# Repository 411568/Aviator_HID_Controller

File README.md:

<h2>🧐 Features</h2>

The goal of this project was to design a HID controller for interfacing a number of buttons and encoders with the X-Plane flight simulator software.

Here're some of the project's best features:

*  11 x button input
*  4 x rotary encoder input
*  1 x I2C interface connector
*  2 x 5V power output
*  USB type C for communication and power
*  HID keyboard interface

<h2>💻 Built with</h2>

Technologies used in the project:

*  STM32F072 microcontroller
*  ST1S06 buck converter
*  USB type C - HID communication
*  2-layer 0.8 mm FR4 PCB

<h2>🛡️ License:</h2>

This project is licensed under the MIT License.

<h2> 🙋‍♂️Authors </h2>

- Krzysztof Sikora

<h2>💖Like my work?</h2>

If you have any questions about the project feel free to contact us via email: krzysieksikora717@gmail.com

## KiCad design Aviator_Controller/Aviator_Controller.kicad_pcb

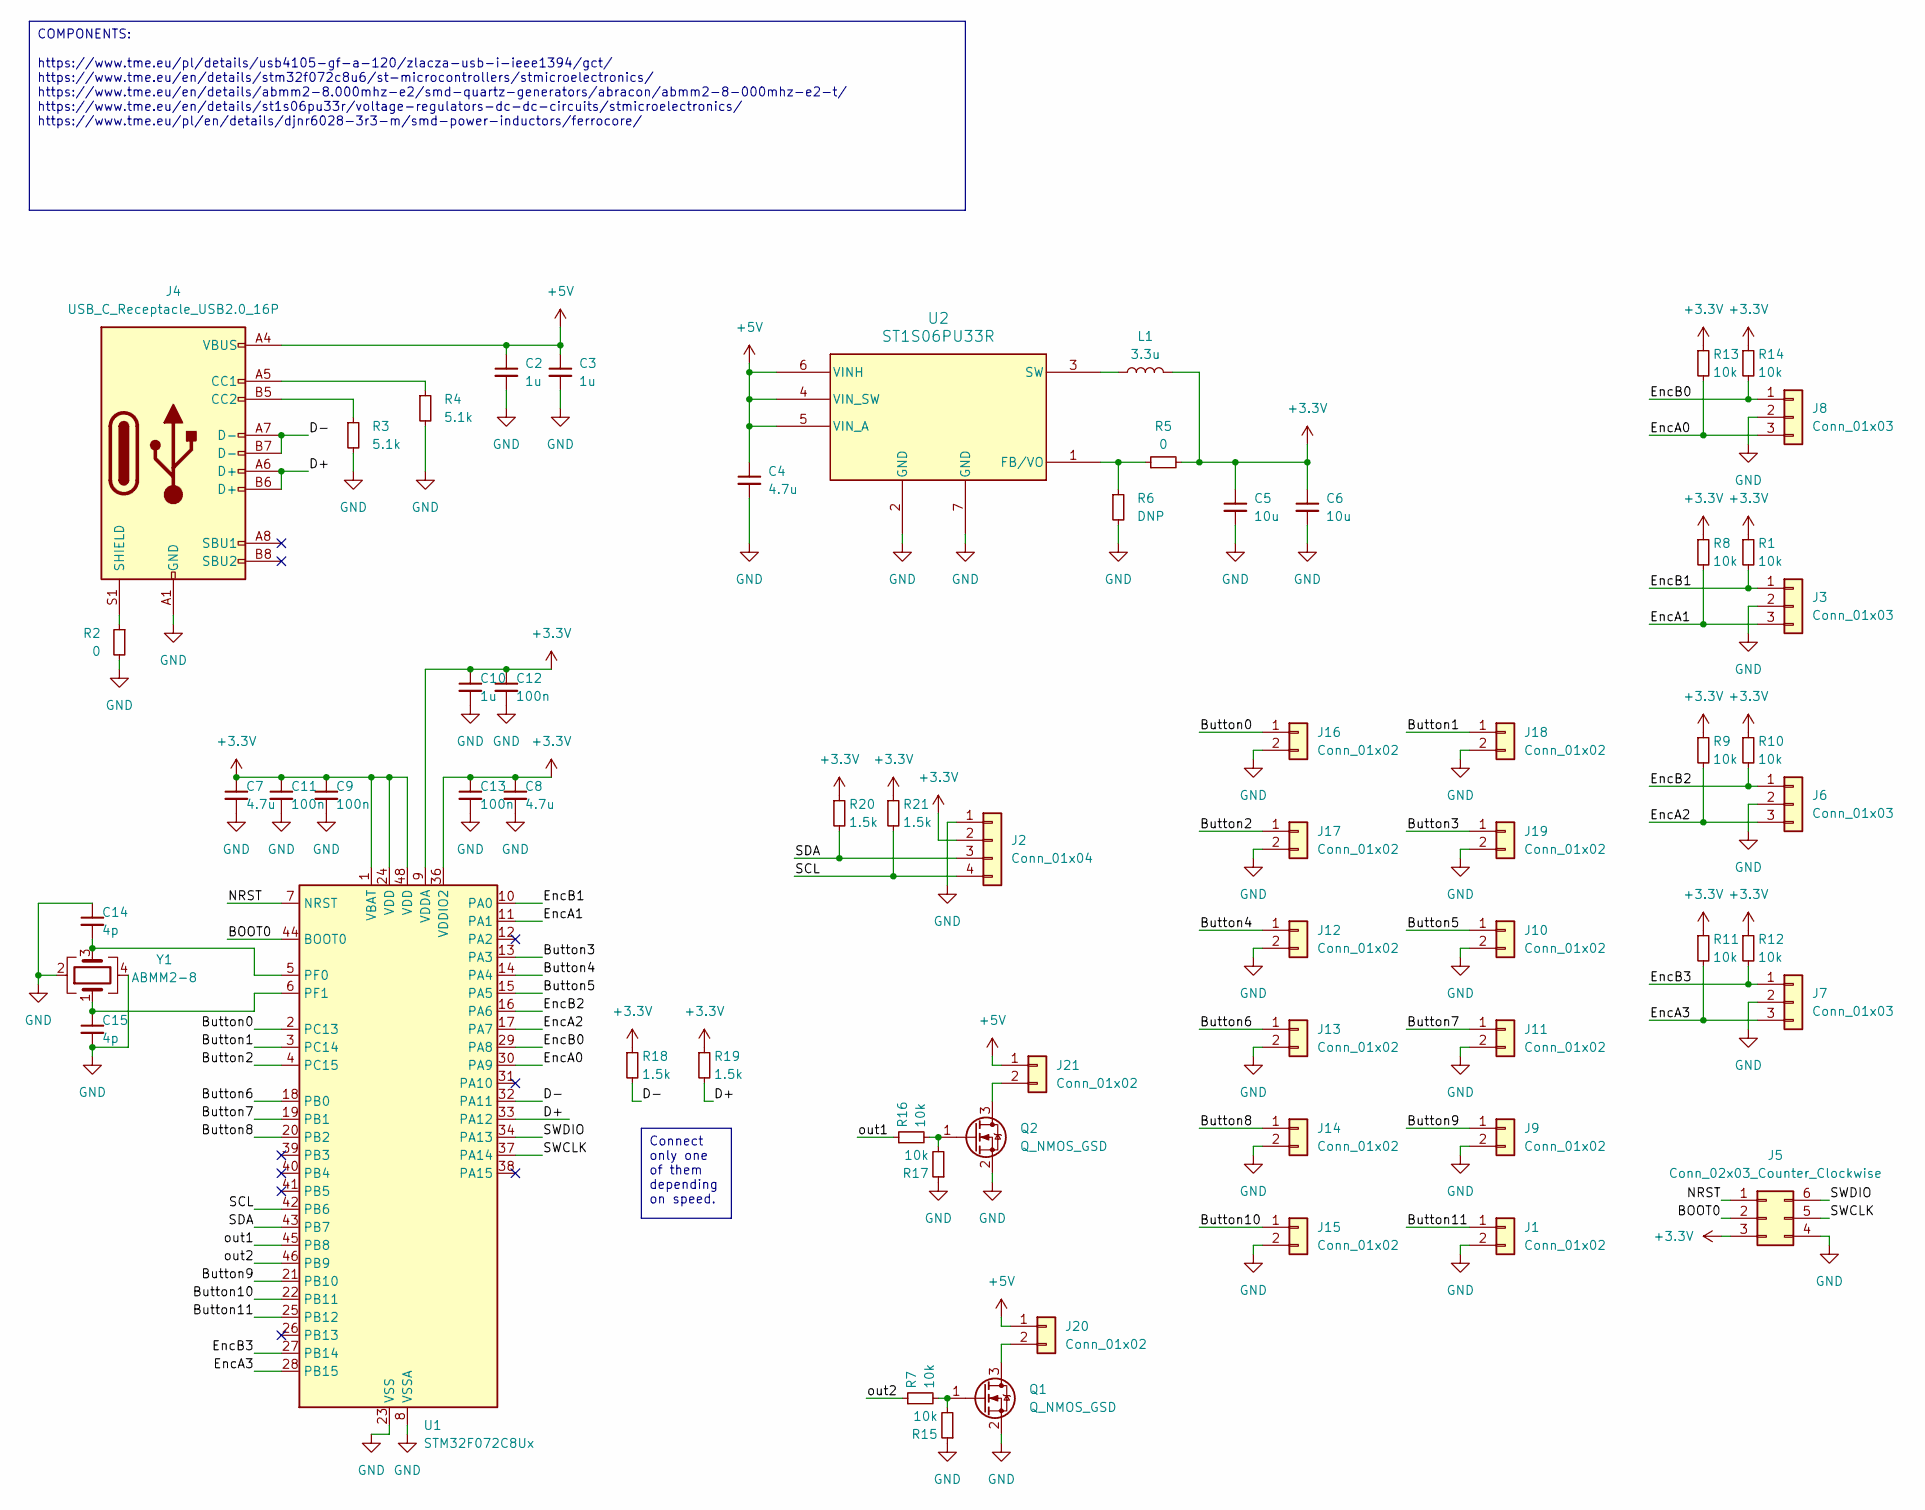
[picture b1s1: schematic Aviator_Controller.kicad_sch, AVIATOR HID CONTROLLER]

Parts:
C2, C3, C10: 1u; C_0603_1608Metric_Pad1.08x0.95mm_HandSolder
C4, C7, C8: 4.7u; C_0805_2012Metric_Pad1.18x1.45mm_HandSolder
C5, C6: 10u; C_0805_2012Metric_Pad1.18x1.45mm_HandSolder
C9, C11, C12, C13: 100n; C_0603_1608Metric_Pad1.08x0.95mm_HandSolder
C14, C15: 4p; C_0603_1608Metric_Pad1.08x0.95mm_HandSolder
J1, J9, J10, J11, J12, J13, J14, J15, J16, J17, J18, J19, J20, J21: Conn_01x02; PinHeader_1x02_P2.54mm_Vertical
J2: Conn_01x04; PinHeader_1x04_P2.54mm_Vertical
J3, J6, J7, J8: Conn_01x03; PinHeader_1x03_P2.54mm_Vertical
J4: USB_C_Receptacle_USB2.0_16P; GCT_USB4105GFA120
J5: Conn_02x03_Counter_Clockwise; PinHeader_2x03_P2.54mm_Vertical
L1: 3.3u; L_Bourns-SRN6028
Q1, Q2: Q_NMOS_GSD; SOT-23
R1, R7, R8, R9, R10, R11, R12, R13, R14, R15, R16, R17: 10k; R_0603_1608Metric_Pad0.98x0.95mm_HandSolder
R2, R5: 0; R_0603_1608Metric_Pad0.98x0.95mm_HandSolder
R3, R4: 5.1k; R_0603_1608Metric_Pad0.98x0.95mm_HandSolder
R6: DNP; R_0603_1608Metric_Pad0.98x0.95mm_HandSolder
R18, R19, R20, R21: 1.5k; R_0603_1608Metric_Pad0.98x0.95mm_HandSolder
U1: STM32F072C8Ux; QFN-48-1EP_7x7mm_P0.5mm_EP5.6x5.6mm
U2: ST1S06PU33R; DFN_6PU33R_STM
Y1: ABMM2-8; XTAL_ABMM2-8.000MHZ-E2-T

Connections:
+3.3V: C5.1, C6.1, C7.1, C8.1, C9.1, C10.1, C11.1, C12.1, C13.1, J2.2, J5.3, L1.2, R1.1, R5.2, R8.1, R9.1, R10.1, R11.1, R12.1, R13.1, R14.1, R18.1, R19.1, R20.1, R21.1, U1.1 (VBAT), U1.9 (VDDA), U1.24 (VDD), U1.36 (VDDIO2), U1.48 (VDD)
+5V: C2.1, C3.1, C4.1, J4.A4 (VBUS), J4.A9 (VBUS), J4.B4 (VBUS), J4.B9 (VBUS), J20.1, J21.1, U2.4 (VIN_SW), U2.5 (VIN_A), U2.6 (VINH)
/BOOT0: J5.2, U1.44 (BOOT0)
/Button0: J16.1, U1.2 (PC13)
/Button1: J18.1, U1.3 (PC14)
/Button2: J17.1, U1.4 (PC15)
/Button3: J19.1, U1.13 (PA3)
/Button4: J12.1, U1.14 (PA4)
/Button5: J10.1, U1.15 (PA5)
/Button6: J13.1, U1.18 (PB0)
/Button7: J11.1, U1.19 (PB1)
/Button8: J14.1, U1.20 (PB2)
/Button9: J9.1, U1.21 (PB10)
/Button10: J15.1, U1.22 (PB11)
/Button11: J1.1, U1.25 (PB12)
/D+: J4.A6 (D+), J4.B6 (D+), R19.2, U1.33 (PA12)
/D-: J4.A7 (D-), J4.B7 (D-), R18.2, U1.32 (PA11)
/EncA0: J8.3, R13.2, U1.30 (PA9)
/EncA1: J3.3, R8.2, U1.11 (PA1)
/EncA2: J6.3, R9.2, U1.17 (PA7)
/EncA3: J7.3, R11.2, U1.28 (PB15)
/EncB0: J8.1, R14.2, U1.29 (PA8)
/EncB1: J3.1, R1.2, U1.10 (PA0)
/EncB2: J6.1, R10.2, U1.16 (PA6)
/EncB3: J7.1, R12.2, U1.27 (PB14)
/NRST: J5.1, U1.7 (NRST)
/SCL: J2.4, R21.2, U1.42 (PB6)
/SDA: J2.3, R20.2, U1.43 (PB7)
/SWCLK: J5.5, U1.37 (PA14)
/SWDIO: J5.6, U1.34 (PA13)
/out1: R16.1, U1.45 (PB8)
/out2: R7.1, U1.46 (PB9)
GND: C2.2, C3.2, C4.2, C5.2, C6.2, C7.2, C8.2, C9.2, C10.2, C11.2, C12.2, C13.2, C14.1, C15.2, J1.2, J2.1, J3.2, J4.A1 (GND), J4.A12 (GND), J4.B1 (GND), J4.B12 (GND), J5.4, J6.2, J7.2, J8.2, J9.2, J10.2, J11.2, J12.2, J13.2, J14.2, J15.2, J16.2, J17.2, J18.2, J19.2, Q1.2 (S), Q2.2 (S), R2.2, R3.2, R4.2, R6.2, R15.1, R17.1, U1.8 (VSSA), U1.23 (VSS), U1.35 (VSS), U1.47 (VSS), U1.49 (VSS), U2.2 (GND), U2.7 (GND), Y1.2, Y1.4
unnamed: J4.A5 (CC1), R4.1
unnamed: J4.B5 (CC2), R3.1
unnamed: J4.S1 (SHIELD), R2.1
unnamed: J20.2, Q1.3 (D)
unnamed: J21.2, Q2.3 (D)
unnamed: Q1.1 (G), R7.2, R15.2
unnamed: Q2.1 (G), R16.2, R17.2
unnamed: C14.2, U1.5 (PF0), Y1.3
unnamed: C15.1, U1.6 (PF1), Y1.1
unnamed: R5.1, R6.1, U2.1 (FB/VO)
unnamed: L1.1, U2.3 (SW)

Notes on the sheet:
Connect only one of them depending on speed.
COMPONENTS: https://www.tme.eu/pl/details/usb4105-gf-a-120/zlacza-usb-i-ieee1394/gct/ https://www.tme.eu/en/details/stm32f072c8u6/st-microcontrollers/stmicroelectronics/ https://www.tme.eu/en/details/abmm2-8.000mhz-e2/smd-quartz-generators/abracon/abmm2-8-000mhz-e2-t/ https://www.tme.eu/en/details/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

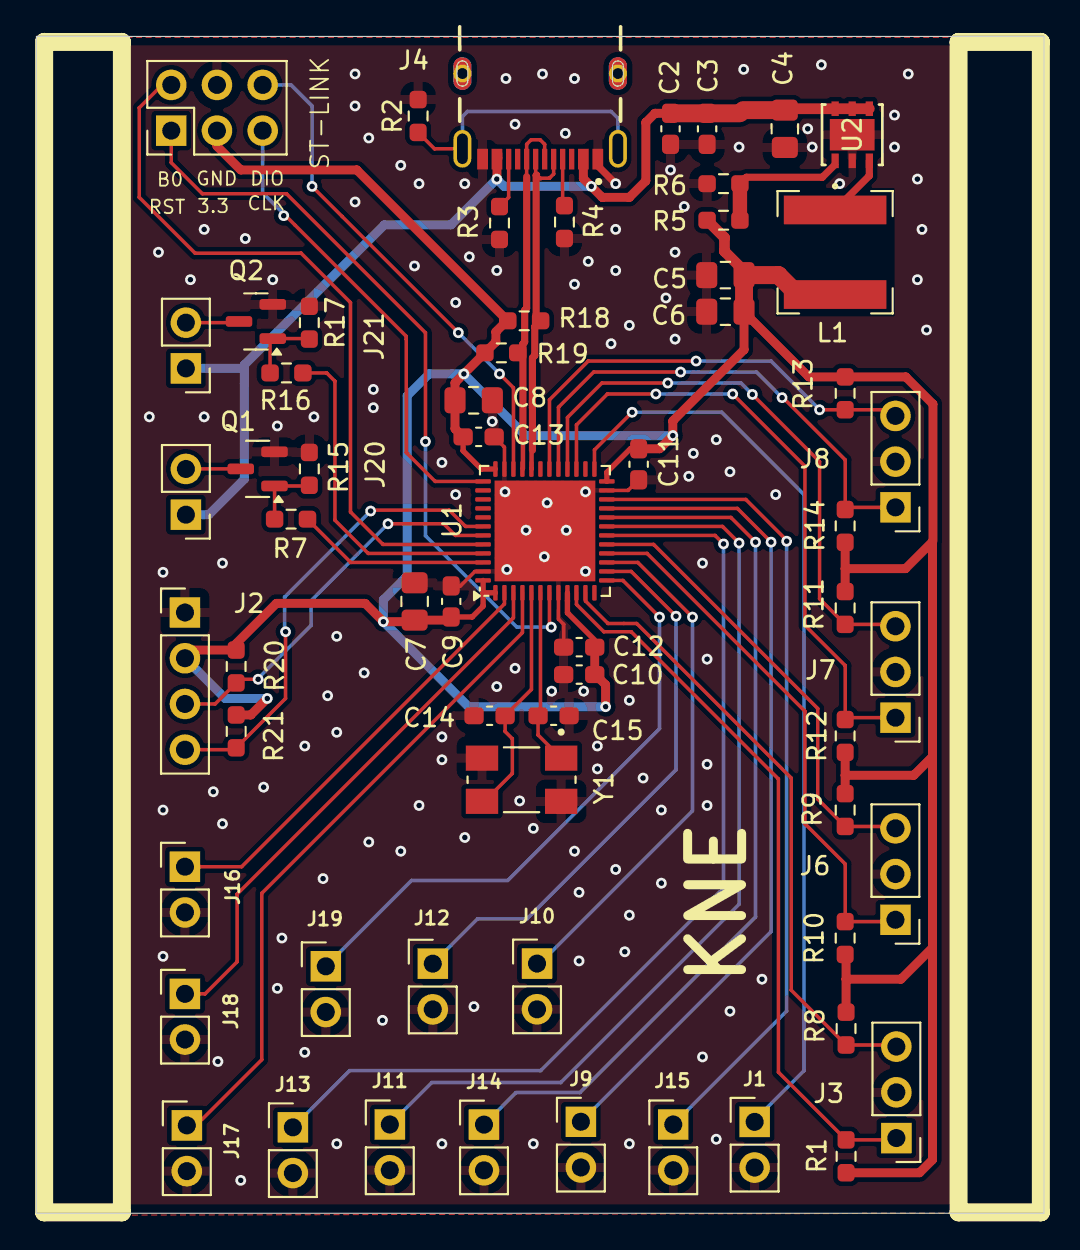
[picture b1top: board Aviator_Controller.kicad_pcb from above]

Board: 2 copper layers, 56.0 x 65.4 mm, 62 parts (0 on the bottom side), 44 nets.

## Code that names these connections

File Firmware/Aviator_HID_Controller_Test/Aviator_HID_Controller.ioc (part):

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Mcu.Name=STM32F072C(8-B)Ux
Mcu.Package=UFQFPN48
Mcu.UserName=STM32F072C8Ux
PA0.GPIOParameters=GPIO_Label
PA0.GPIO_Label=EncB1
PA0.Signal=S_TIM2_CH1_ETR
PA1.GPIOParameters=GPIO_Label
PA1.GPIO_Label=EncA1
PA1.Signal=S_TIM2_CH2
PA11.Mode=Device
PA11.Signal=USB_DM
PA12.Mode=Device
PA12.Signal=USB_DP
PA13.Mode=Serial_Wire
PA13.Signal=SYS_SWDIO
PA14.Mode=Serial_Wire
PA14.Signal=SYS_SWCLK
PA3.GPIOParameters=GPIO_PuPd,GPIO_Label
PA3.GPIO_Label=Button3
PA3.GPIO_PuPd=GPIO_PULLUP
PA3.Signal=GPIO_Input
PA4.GPIOParameters=GPIO_PuPd,GPIO_Label
PA4.GPIO_Label=Button4
PA4.GPIO_PuPd=GPIO_PULLUP
PA4.Signal=GPIO_Input
PA5.GPIOParameters=GPIO_PuPd,GPIO_Label
PA5.GPIO_Label=Button5
PA5.GPIO_PuPd=GPIO_PULLUP
PA5.Signal=GPIO_Input
PA6.GPIOParameters=GPIO_Label
PA6.GPIO_Label=EncB2
PA6.Signal=S_TIM3_CH1
PA7.GPIOParameters=GPIO_Label
PA7.GPIO_Label=EncA2
PA7.Signal=S_TIM3_CH2
PA8.GPIOParameters=GPIO_Label
PA8.GPIO_Label=EncB0
PA8.Signal=S_TIM1_CH1
PA9.GPIOParameters=GPIO_Label
PA9.GPIO_Label=EncA0
PA9.Signal=S_TIM1_CH2
PB0.GPIOParameters=GPIO_PuPd,GPIO_Label
PB0.GPIO_Label=Button6
PB0.GPIO_PuPd=GPIO_PULLUP
PB0.Signal=GPIO_Input
PB1.GPIOParameters=GPIO_PuPd,GPIO_Label
PB1.GPIO_Label=Button7
PB1.GPIO_PuPd=GPIO_PULLUP
PB1.Signal=GPIO_Input
PB10.GPIOParameters=GPIO_PuPd,GPIO_Label
PB10.GPIO_Label=Button9
PB10.GPIO_PuPd=GPIO_PULLUP
PB10.Signal=GPIO_Input
PB11.GPIOParameters=GPIO_PuPd,GPIO_Label
PB11.GPIO_Label=Button10
PB11.GPIO_PuPd=GPIO_PULLUP
PB11.Signal=GPIO_Input
PB12.GPIOParameters=GPIO_PuPd,GPIO_Label
PB12.GPIO_Label=Button11
PB12.GPIO_PuPd=GPIO_PULLUP
PB12.Signal=GPIO_Input
PB2.GPIOParameters=GPIO_PuPd,GPIO_Label
PB2.GPIO_Label=Button8
PB2.GPIO_PuPd=GPIO_PULLUP
PB2.Signal=GPIO_Input
PB6.Mode=I2C
PB6.Signal=I2C1_SCL
PB7.Mode=I2C
PB7.Signal=I2C1_SDA
PB8.GPIOParameters=GPIO_Label
PB8.GPIO_Label=out1
PB8.Signal=GPIO_Output
PB9.GPIOParameters=GPIO_Label
PB9.GPIO_Label=out2
PB9.Signal=GPIO_Output
PC13.GPIOParameters=GPIO_PuPd,GPIO_Label
PC13.GPIO_Label=Button0
PC13.GPIO_PuPd=GPIO_PULLUP
PC13.Signal=GPIO_Input
PC14-OSC32_IN.GPIOParameters=GPIO_PuPd,GPIO_Label
PC14-OSC32_IN.GPIO_Label=Button1
PC14-OSC32_IN.GPIO_PuPd=GPIO_PULLUP
PC14-OSC32_IN.Signal=GPIO_Input
PC15-OSC32_OUT.GPIOParameters=GPIO_PuPd,GPIO_Label
PC15-OSC32_OUT.GPIO_Label=Button2
PC15-OSC32_OUT.GPIO_PuPd=GPIO_PULLUP
PC15-OSC32_OUT.Signal=GPIO_Input
PF0-OSC_IN.Mode=HSE-External-Oscillator
PF0-OSC_IN.Signal=RCC_OSC_IN
PF1-OSC_OUT.Mode=HSE-External-Oscillator
PF1-OSC_OUT.Signal=RCC_OSC_OUT
RCC.SYSCLKFreq_VALUE=48000000
RCC.SYSCLKSource=RCC_SYSCLKSOURCE_HSI48
board=custom

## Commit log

2024-12-22 created kicad project
2024-12-23 added the pcb project v0.1
2025-01-19 added readme
2025-01-19 Create LICENSE
2025-02-12 Added test firmware'
2025-02-17 Changed the button read from EXTI to polling
